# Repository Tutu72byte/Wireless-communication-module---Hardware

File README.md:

# Wireless Expansion & Processing Module (TIE2023 Contest Subject)

## General Description

This hardware project is a high-performance **wireless communication expansion module**
designed as a plug-in card with a 75-pin card-edge interface (compatible with M.2/PCI standards). 

Built around an advanced wireless SoC (referred to in the schematic as **TIE2023**), the module is engineered for 
compact applications requiring wireless connectivity, high-speed data storage, and efficient power management.

---

## Architecture & Functional Blocks

The board integrates several major functional sections:

1. **Central Processing & Wireless Unit (SoC - TIE2023):**
   * Dedicated chip for embedded applications and wireless protocols.
   * Integrated high-speed peripherals, including USB lines (`USB_D+`, `USB_D-`) and PCI differential pairs (`PERP0`/`PERN0`, `PETP0`/`PETN0`).
   * External antenna support through two dedicated RF ports with U.FL connectors (`J1`, `J2`) and optimized impedance matching networks.

2. **Non-Volatile Storage (QSPI Flash):**
   * Features the **MX25R6435F** (64Mb Serial Multi-I/O Flash) memory connected via a high-speed QSPI bus for firmware storage, file systems, or configuration data.

3. **Power Management System:**
   * **DC-DC Regulator:** Based on the Texas Instruments **TPS562810-Q1** step-down regulator, generating a stable internal supply voltage (`VDD`) from the main input rail (`VIN`).

4. **Interface (Card-Edge / Bus - J3):**
   * A 75-pin card-edge connection providing power rails, high-speed data buses (USB/PCIe), and control/status signals (`W_DISABLE1`, `W_DISABLE2`, alert lines)

---

## PCB Layout & Design Guidelines
The printed circuit board (PCB) was routed following various good practices such as:

* **4-Layer Stackup Strategy:**
  * **Layer 1 (Top):** Primary component placement, critical RF traces leading to U.FL connectors, and high-speed signals.
  * **Layer 2 (Inner 1 - Ground Plane):** A solid, continuous internal ground plane (`GND`) ensuring a low-impedance return path for high-speed signals and effective electromagnetic shielding (EMI).
  * **Layer 3 (Inner 2 - Power Plane):** Split power planes dedicated to distributing various supply voltages cleanly across the board.
  * **Layer 4 (Bottom):** Secondary routing layer.
* **High-Speed Routing:** Differential pairs (such as USB and PCIe lines) were routed with controlled impedance and matched lengths to preserve signal integrity (Within the limits of the footprints and pads dimensions).
* **Component Placement & Decoupling:** 
  * All decoupling capacitors were placed as close as possible to the power pins of their respective ICs to minimize parasitic inductance and noise (Especially on the bottom right of the board where the converter sits).
  * Quartz crystal oscillators (`Y1`, `Y2`) were positioned directly adjacent to their target chips to ensure clean clock generation.
* **Test Points:** Dedicated test points (`TP1`, `TP3`, `TP4`, `TP5`) were strategically placed on the board to facilitate hardware debugging, signal probing, and manufacturing verification.

---

## Technical Specifications

* **Power Input:** `VIN` converted internally to `VDD` via the `TPS562810-Q1` buck regulator.
* **Storage:** 64Mb Serial Flash (`MX25R6435F`).
* **Connectivity & Interfaces:** 
  * High-speed USB and PCIe links.
  * Dual U.FL RF ports for external antennas.
  * Integrated NFC capability.
* **Status Indication:** 3 status LEDs (`LED1`, `LED2`, `LED3`).

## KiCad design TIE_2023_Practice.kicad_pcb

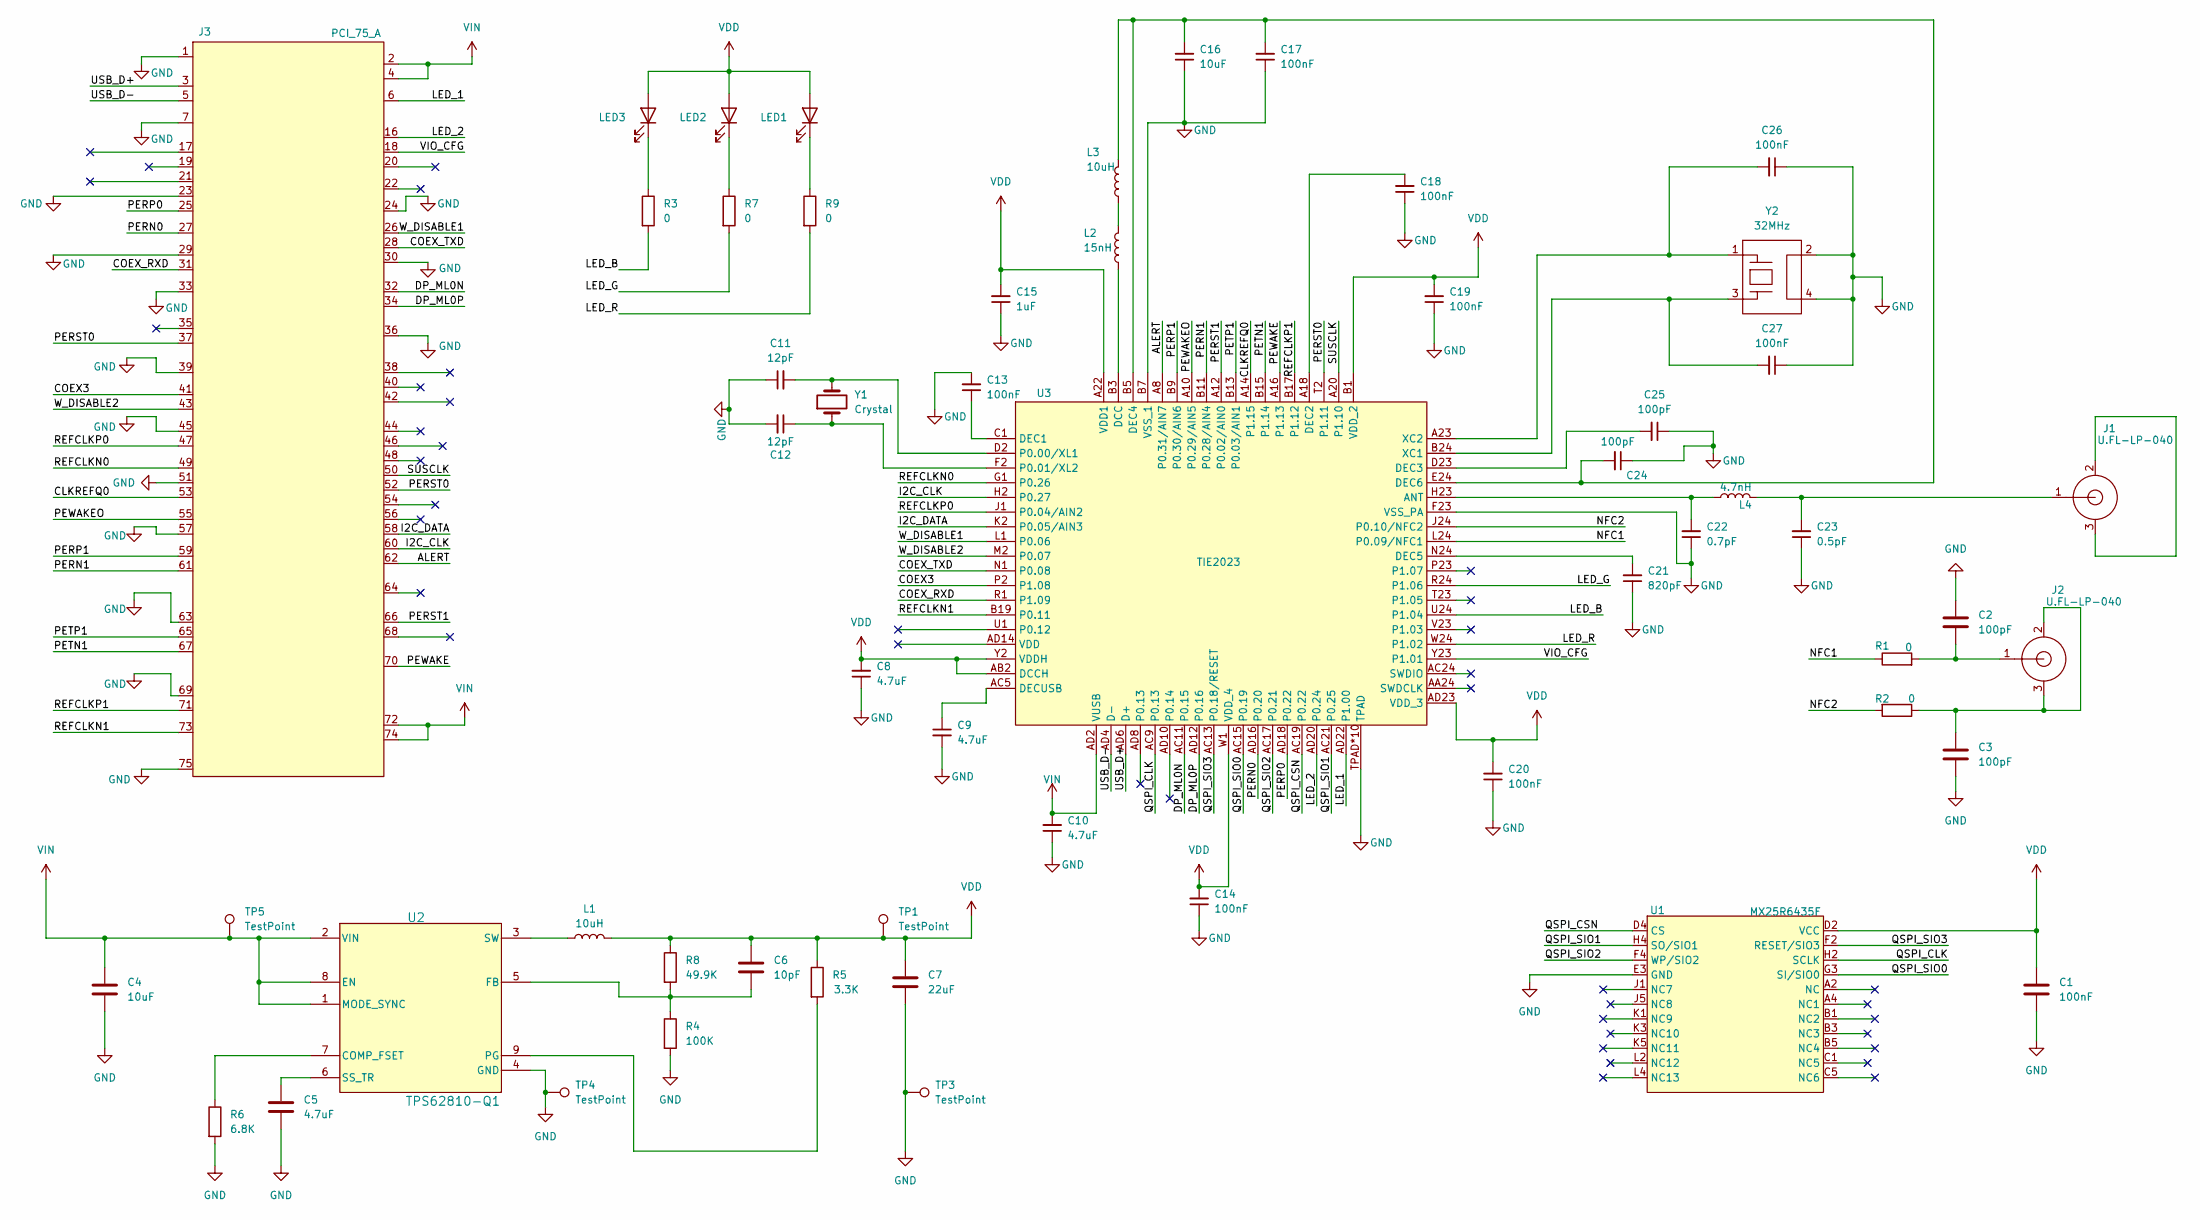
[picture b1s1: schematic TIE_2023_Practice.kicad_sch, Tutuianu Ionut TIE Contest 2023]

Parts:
C1: 100nF; C_0402_1005Metric_Pad0.74x0.62mm_HandSolder
C2, C3: 100pF; C_0402_1005Metric_Pad0.74x0.62mm_HandSolder
C4: 10uF; C_0805_2012Metric_Pad1.18x1.45mm_HandSolder
C5: 4.7uF; C_0201_0603Metric_Pad0.64x0.40mm_HandSolder
C6: 10pF; C_0201_0603Metric_Pad0.64x0.40mm_HandSolder
C7: 22uF; C_0805_2012Metric_Pad1.18x1.45mm_HandSolder
C8, C9: 4.7uF; C_0201_0603Metric
C10: 4.7uF; C_01005_0402Metric
C11, C12: 12pF; C_01005_0402Metric
C13, C14, C17, C18, C19, C20, C26, C27: 100nF; C_01005_0402Metric
C15: 1uF; C_01005_0402Metric
C16: 10uF; C_0201_0603Metric
C21: 820pF; C_0201_0603Metric
C22: 0.7pF; C_01005_0402Metric
C23: 0.5pF; C_01005_0402Metric
C24, C25: 100pF; C_0201_0603Metric
J1, J2: U.FL-LP-040; Coaxial FL-LP-040
J3: PCI_75_A; PCI_75
L1: 10uH; L_1206_3216Metric_Pad1.22x1.90mm_HandSolder
L2: 15nH; L_0201_0603Metric
L3: 10uH; L_0201_0603Metric
L4: 4.7nH; L_0201_0603Metric
LED1, LED2, LED3: LED_0402_1005Metric_Pad0.77x0.64mm_HandSolder
R1, R2, R3, R7, R9: 0; R_0402_1005Metric_Pad0.72x0.64mm_HandSolder
R4: 100K; R_0201_0603Metric_Pad0.64x0.40mm_HandSolder
R5: 3.3K; R_0201_0603Metric_Pad0.64x0.40mm_HandSolder
R6: 6.8K; R_0201_0603Metric_Pad0.64x0.40mm_HandSolder
R8: 49.9K; R_0201_0603Metric_Pad0.64x0.40mm_HandSolder
TP1, TP3, TP4: TestPoint; TestPoint_Pad_D1.0mm
TP5: TestPoint; TestPoint_Pad_D2.0mm
U1: MX25R6435F; MX25R64
U2: TPS62810-Q1; RWY0009
U3: TIE2023; Component_TIE2023
Y1: Crystal; CPFX-217 Crystal
Y2: 32MHz; Q_XRCGB30

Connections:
/ALERT: J3.62, U3.A8 (P0.31/AIN7)
/CLKREFQ0: J3.53, U3.A14 (P1.15)
/COEX3: J3.41, U3.P2 (P1.08)
/COEX_RXD: J3.31, U3.R1 (P1.09)
/COEX_TXD: J3.28, U3.N1 (P0.08)
/DP_ML0N: J3.32, U3.AC11 (P0.15)
/DP_ML0P: J3.34, U3.AD12 (P0.16)
/I2C_CLK: J3.60, U3.H2 (P0.27)
/I2C_DATA: J3.58, U3.K2 (P0.05/AIN3)
/LED_1: J3.6, U3.AD22 (P1.00)
/LED_2: J3.16, U3.AD20 (P0.24)
/LED_B: R3.2, U3.U24 (P1.04)
/LED_G: R7.2, U3.R24 (P1.06)
/LED_R: R9.2, U3.W24 (P1.02)
/NFC1: R1.1, U3.L24 (P0.09/NFC1)
/NFC2: R2.2, U3.J24 (P0.10/NFC2)
/PERN0: J3.27, U3.AD16 (P0.20)
/PERN1: J3.61, U3.B11 (P0.28/AIN4)
/PERP0: J3.25, U3.AD18 (P0.22)
/PERP1: J3.59, U3.B9 (P0.30/AIN6)
/PERST0: J3.37, J3.52, U3.T2 (P1.11)
/PERST1: J3.66, U3.A12 (P0.02/AIN0)
/PETN1: J3.67, U3.B15 (P1.14)
/PETP1: J3.65, U3.B13 (P0.03/AIN1)
/PEWAKE: J3.70, U3.A16 (P1.13)
/PEWAKEO: J3.55, U3.A10 (P0.29/AIN5)
/QSPI_CLK: U1.H2 (SCLK), U3.AC9 (P0.13)
/QSPI_CSN: U1.D4 (CS), U3.AC19 (P0.22)
/QSPI_SIO0: U1.G3 (SI/SIO0), U3.AC15 (P0.19)
/QSPI_SIO1: U1.H4 (SO/SIO1), U3.AC21 (P0.25)
/QSPI_SIO2: U1.F4 (WP/SIO2), U3.AC17 (P0.21)
/QSPI_SIO3: U1.F2 (RESET/SIO3), U3.AC13 (P0.18/RESET)
/REFCLKN0: J3.49, U3.G1 (P0.26)
/REFCLKN1: J3.73, U3.B19 (P0.11)
/REFCLKP0: J3.47, U3.J1 (P0.04/AIN2)
/REFCLKP1: J3.71, U3.B17 (P1.12)
/SUSCLK: J3.50, U3.A20 (P1.10)
/USB_D+: J3.3, U3.AD6 (D+)
/USB_D-: J3.5, U3.AD4 (D-)
/VIO_CFG: J3.18, U3.Y23 (P1.01)
/W_DISABLE1: J3.26, U3.L1 (P0.06)
/W_DISABLE2: J3.43, U3.M2 (P0.07)
GND: C1.2, C2.1, C3.2, C4.2, C5.2, C7.2, C8.1, C9.2, C10.1, C11.1, C12.2, C13.2, C14.1, C15.1, C16.1, C17.1, C18.1, C19.1, C20.1, C21.1, C22.1, C23.1, C24.1, C25.1, C26.1, C27.1, J3.1, J3.7, J3.23, J3.24, J3.29, J3.30, J3.33, J3.36, J3.39, J3.45, J3.51, J3.57, J3.63, J3.69, J3.75, R4.2, R6.2, TP3.1, TP4.1, U1.E3 (GND), U2.4 (GND), U3.B7 (VSS_1), U3.F23 (VSS_PA), U3.TPAD*10 (TPAD), Y2.2, Y2.4
unnamed: C2.2, J2.1, R1.2
unnamed: C3.1, J2.2, J2.3, R2.1
unnamed: C23.2, J1.1, L4.2
unnamed: J1.2, J1.3
unnamed: L2.2, L3.1
unnamed: LED1.1 (K), R9.1
unnamed: LED2.1 (K), R7.1
unnamed: LED3.1 (K), R3.1
unnamed: R6.1, U2.7 (COMP_FSET)
unnamed: C6.2, R4.1, R8.2, U2.5 (FB)
unnamed: R5.2, U2.9 (PG)
unnamed: C5.1, U2.6 (SS_TR)
unnamed: L1.1, U2.3 (SW)
unnamed: C22.2, L4.1, U3.H23 (ANT)
unnamed: L2.1, U3.B3 (DCC)
unnamed: C13.1, U3.C1 (DEC1)
unnamed: C18.2, U3.A18 (DEC2)
unnamed: C25.2, U3.D23 (DEC3)
unnamed: C16.2, C17.2, C24.2, L3.2, U3.B5 (DEC4), U3.E24 (DEC6)
unnamed: C21.2, U3.N24 (DEC5)
unnamed: C9.1, U3.AC5 (DECUSB)
unnamed: C11.2, U3.D2 (P0.00/XL1), Y1.2
unnamed: C12.1, U3.F2 (P0.01/XL2), Y1.1
unnamed: C27.2, U3.B24 (XC1), Y2.3
unnamed: C26.2, U3.A23 (XC2), Y2.1
VDD: C1.1, C6.1, C7.1, C8.2, C14.2, C15.2, C19.2, C20.2, L1.2, LED1.2 (A), LED2.2 (A), LED3.2 (A), R5.1, R8.1, TP1.1, U1.D2 (VCC), U3.A22 (VDD1), U3.AB2 (DCCH), U3.AD23 (VDD_3), U3.B1 (VDD_2), U3.W1 (VDD_4), U3.Y2 (VDDH)
VIN: C4.1, C10.2, J3.2, J3.4, J3.72, J3.74, TP5.1, U2.1 (MODE_SYNC), U2.2 (VIN), U2.8 (EN), U3.AD2 (VUSB)

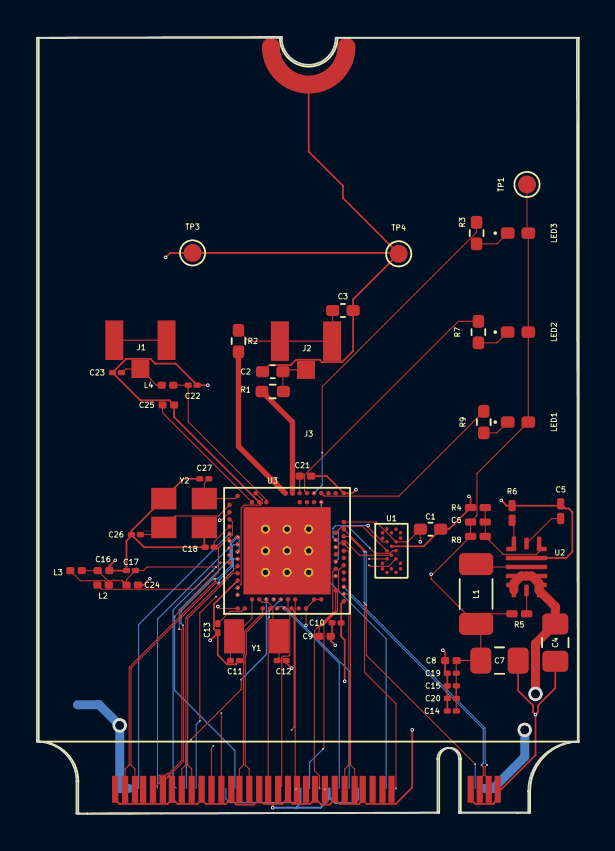
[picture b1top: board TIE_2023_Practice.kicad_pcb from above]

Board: 4 copper layers, 30.0 x 43.2 mm, 55 parts (1 on the bottom side), 70 nets.
